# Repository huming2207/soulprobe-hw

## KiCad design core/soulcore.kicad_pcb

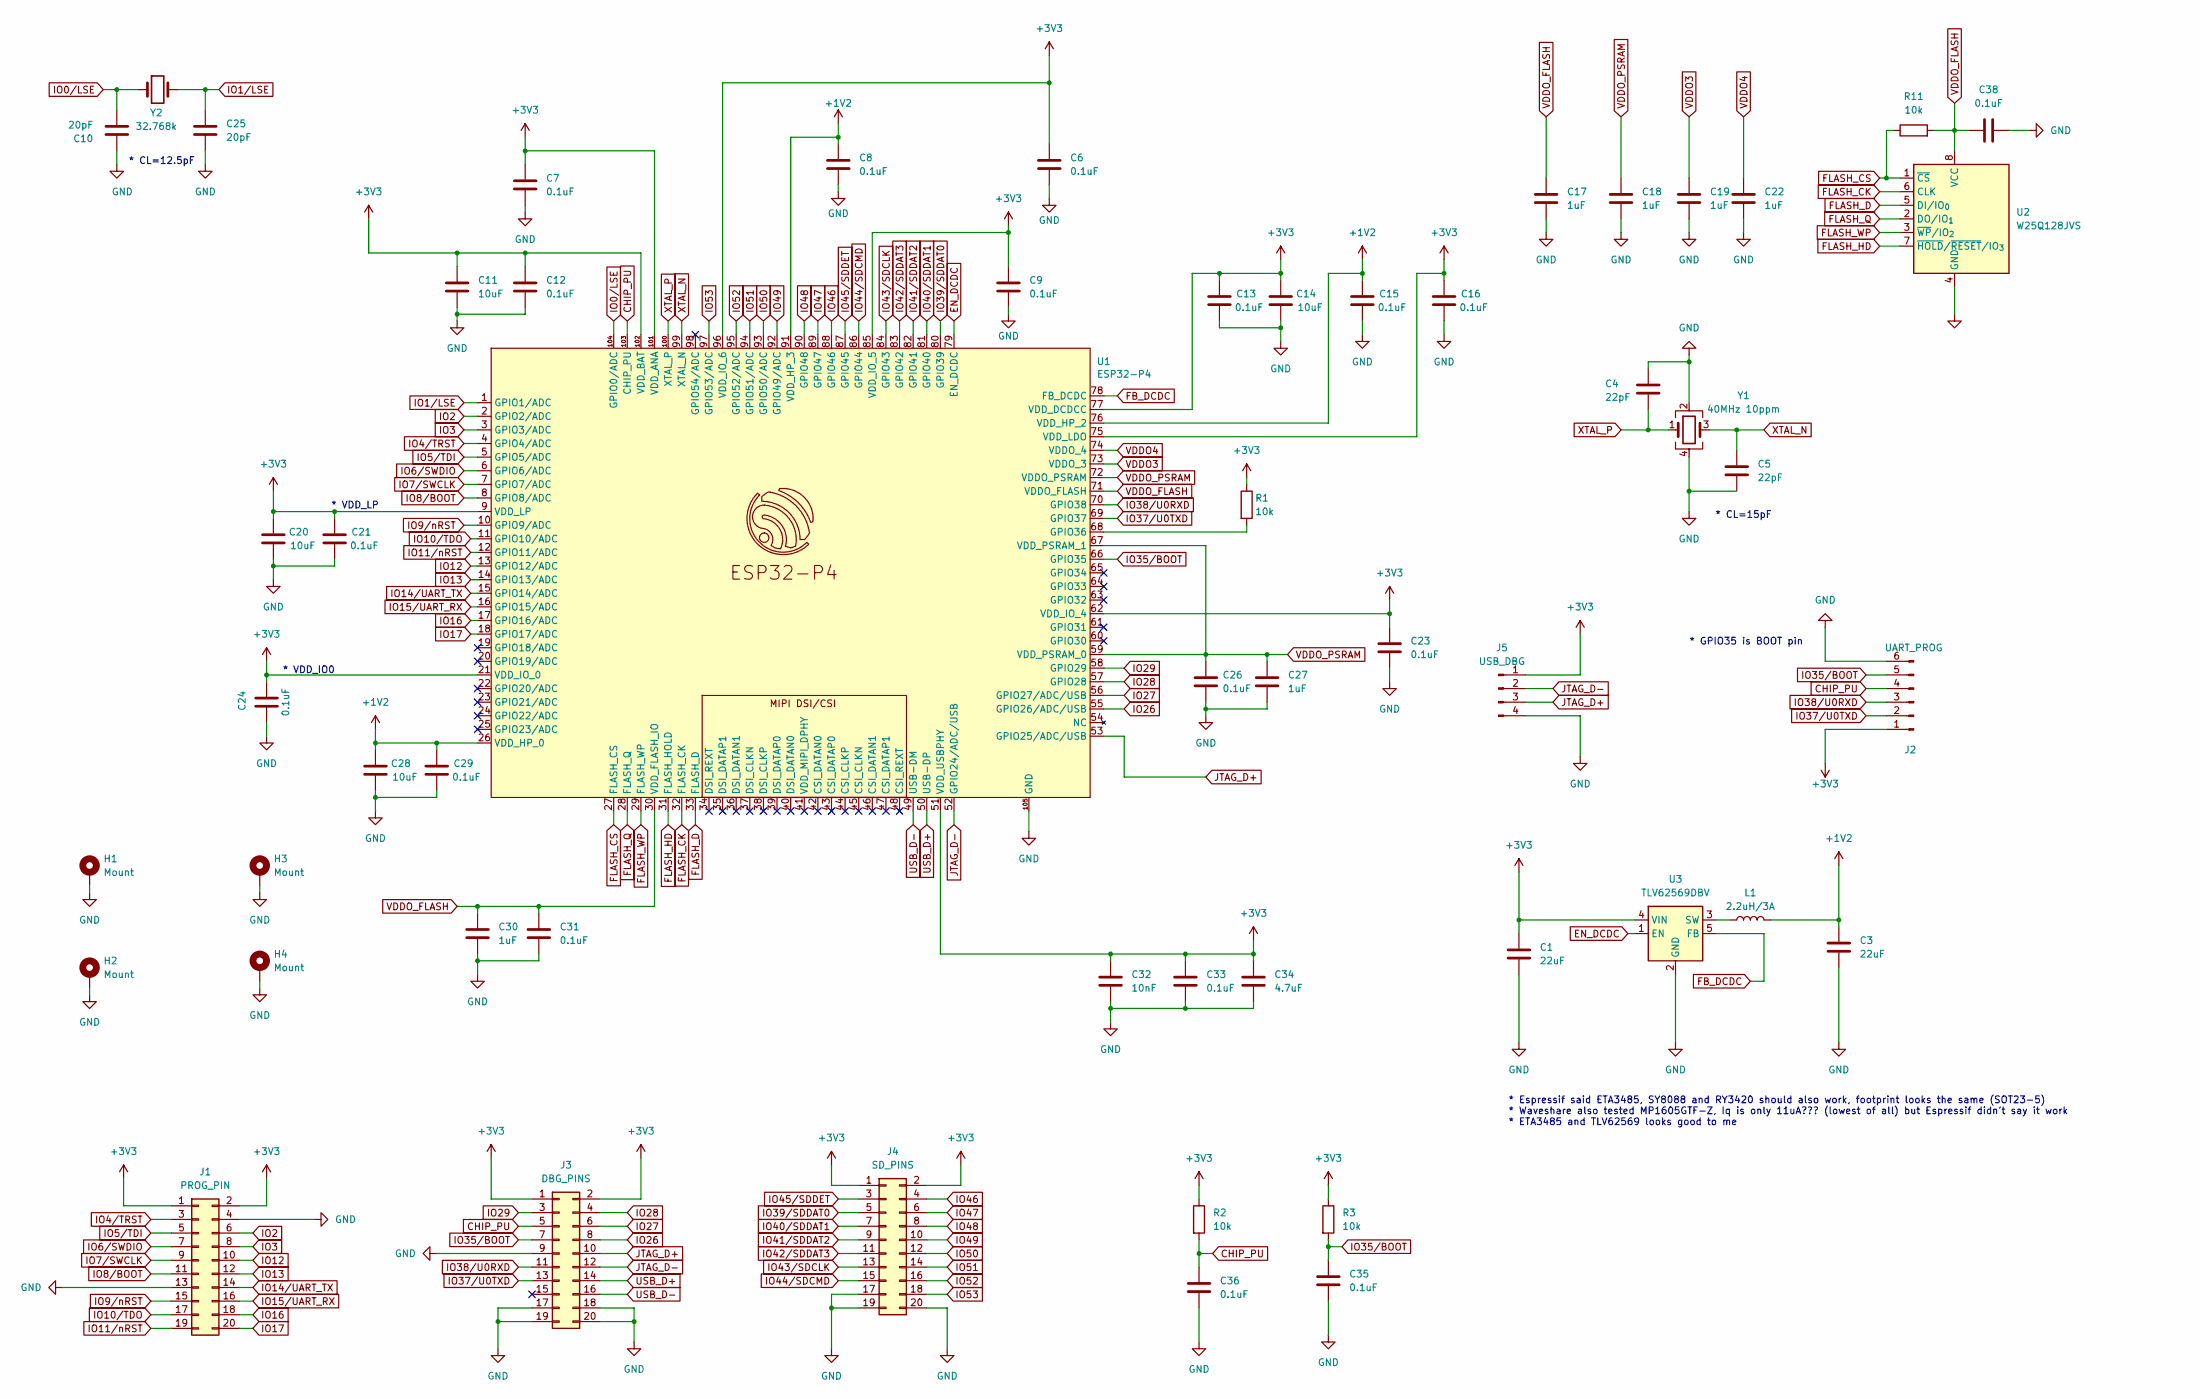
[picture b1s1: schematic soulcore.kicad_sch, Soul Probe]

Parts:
C1, C3: 22uF; C_0402_1005Metric; LCSC C59461
C4, C5: 22pF; C_0402_1005Metric; LCSC C1555
C6, C7, C8, C9, C12, C13, C15, C16, C21, C23, C24, C26, C29, C31, C33, C35, C36, C38: 0.1uF; C_0402_1005Metric; LCSC C1525
C10, C25: 20pF; C_0402_1005Metric; LCSC C1554
C11, C14, C20, C28: 10uF; C_0402_1005Metric; LCSC C19702
C17, C18, C19, C22, C27, C30: 1uF; C_0402_1005Metric; LCSC C15849
C32: 10nF; C_0402_1005Metric; LCSC C57112
C34: 4.7uF; C_0402_1005Metric; LCSC C19666
H1, H2, H3, H4: Mount; MountingHole_2.2mm_M2_Pad
J1: PROG_PIN; PinHeader_2x10_P1.27mm_Vertical_SMD
J2: UART_PROG; PinSocket_1x06_P2.00mm_Vertical
J3: DBG_PINS; PinHeader_2x10_P1.27mm_Vertical_SMD
J4: SD_PINS; PinHeader_2x10_P1.27mm_Vertical_SMD
J5: USB_DBG; PinSocket_1x04_P2.00mm_Vertical
L1: 2.2uH/3A; L_Changjiang_FTC322510S; LCSC C5832385
R1, R2, R3, R11: 10k; R_0402_1005Metric; LCSC C25744
U1: ESP32-P4; LCSC C22387510
U2: W25Q128JVS; SOIC-8_5.3x5.3mm_P1.27mm; LCSC C97521
U3: TLV62569DBV; SOT-23-5; LCSC C141836
Y1: 40MHz 10ppm; Crystal_SMD_2016-4Pin_2.0x1.6mm; LCSC C424432
Y2: 32.768k; Crystal_SMD_3215-2Pin_3.2x1.5mm; LCSC C32346

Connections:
+1V2: C3.1, C8.1, C15.1, C28.1, C29.1, L1.2, U1.26 (VDD_HP_0), U1.76 (VDD_HP_2), U1.91 (VDD_HP_3)
+3V3: C1.1, C6.1, C7.1, C9.1, C11.1, C12.1, C13.1, C14.1, C16.1, C20.1, C21.1, C23.1, C24.2, C32.1, C33.1, C34.1, J1.1, J1.2, J2.1, J3.1, J3.2, J4.1, J4.2, J5.1, R1.1, R2.1, R3.1, U1.9 (VDD_LP), U1.21 (VDD_IO_0), U1.51 (VDD_USBPHY), U1.62 (VDD_IO_4), U1.75 (VDD_LDO), U1.77 (VDD_DCDCC), U1.85 (VDD_IO_5), U1.96 (VDD_IO_6), U1.101 (VDD_ANA), U1.102 (VDD_BAT), U3.4 (VIN)
CHIP_PU: C36.1, J2.4, J3.5, R2.2, U1.103 (CHIP_PU)
EN_DCDC: U1.79 (EN_DCDC), U3.1 (EN)
FB_DCDC: U1.78 (FB_DCDC), U3.5 (FB)
FLASH_CK: U1.32 (FLASH_CK), U2.6 (CLK)
FLASH_CS: R11.1, U1.27 (FLASH_CS), U2.1 (~CS)
FLASH_D: U1.33 (FLASH_D), U2.5 (DI/IO_{0})
FLASH_HD: U1.31 (FLASH_HOLD), U2.7 (~HOLD/~RESET/IO_{3})
FLASH_Q: U1.28 (FLASH_Q), U2.2 (DO/IO_{1})
FLASH_WP: U1.29 (FLASH_WP), U2.3 (~WP/IO_{2})
GND: C1.2, C3.2, C4.1, C5.2, C6.2, C7.2, C8.2, C9.2, C10.1, C11.2, C12.2, C13.2, C14.2, C15.2, C16.2, C17.2, C18.2, C19.2, C20.2, C21.2, C22.2, C23.2, C24.1, C25.2, C26.2, C27.2, C28.2, C29.2, C30.2, C31.2, C32.2, C33.2, C34.2, C35.2, C36.2, C38.2, H1.1, H2.1, H3.1, H4.1, J1.4, J1.13, J2.6, J3.9, J3.17, J3.18, J3.19, J3.20, J4.17, J4.19, J4.20, J5.4, U1.105 (GND), U2.4 (GND), U3.2 (GND), Y1.2, Y1.4
IO0/LSE: C10.2, U1.104 (GPIO0/ADC), Y2.1
IO1/LSE: C25.1, U1.1 (GPIO1/ADC), Y2.2
IO2: J1.6, U1.2 (GPIO2/ADC)
IO3: J1.8, U1.3 (GPIO3/ADC)
IO4/TRST: J1.3, U1.4 (GPIO4/ADC)
IO5/TDI: J1.5, U1.5 (GPIO5/ADC)
IO6/SWDIO: J1.7, U1.6 (GPIO6/ADC)
IO7/SWCLK: J1.9, U1.7 (GPIO7/ADC)
IO8/BOOT: J1.11, U1.8 (GPIO8/ADC)
IO9/nRST: J1.15, U1.10 (GPIO9/ADC)
IO10/TDO: J1.17, U1.11 (GPIO10/ADC)
IO11/nRST: J1.19, U1.12 (GPIO11/ADC)
IO12: J1.10, U1.13 (GPIO12/ADC)
IO13: J1.12, U1.14 (GPIO13/ADC)
IO14/UART_TX: J1.14, U1.15 (GPIO14/ADC)
IO15/UART_RX: J1.16, U1.16 (GPIO15/ADC)
IO16: J1.18, U1.17 (GPIO16/ADC)
IO17: J1.20, U1.18 (GPIO17/ADC)
IO26: J3.8, U1.55 (GPIO26/ADC/USB)
IO27: J3.6, U1.56 (GPIO27/ADC/USB)
IO28: J3.4, U1.57 (GPIO28)
IO29: J3.3, U1.58 (GPIO29)
IO35/BOOT: C35.1, J2.5, J3.7, R3.2, U1.66 (GPIO35)
IO37/U0TXD: J2.2, J3.13, U1.69 (GPIO37)
IO38/U0RXD: J2.3, J3.11, U1.70 (GPIO38)
IO39/SDDAT0: J4.5, U1.80 (GPIO39)
IO40/SDDAT1: J4.7, U1.81 (GPIO40)
IO41/SDDAT2: J4.9, U1.82 (GPIO41)
IO42/SDDAT3: J4.11, U1.83 (GPIO42)
IO43/SDCLK: J4.13, U1.84 (GPIO43)
IO44/SDCMD: J4.15, U1.86 (GPIO44)
IO45/SDDET: J4.3, U1.87 (GPIO45)
IO46: J4.4, U1.88 (GPIO46)
IO47: J4.6, U1.89 (GPIO47)
IO48: J4.8, U1.90 (GPIO48)
IO49: J4.10, U1.92 (GPIO49/ADC)
IO50: J4.12, U1.93 (GPIO50/ADC)
IO51: J4.14, U1.94 (GPIO51/ADC)
IO52: J4.16, U1.95 (GPIO52/ADC)
IO53: J4.18, U1.97 (GPIO53/ADC)
JTAG_D+: J3.10, J5.3, U1.53 (GPIO25/ADC/USB)
JTAG_D-: J3.12, J5.2, U1.52 (GPIO24/ADC/USB)
unnamed: R1.2, U1.68 (GPIO36)
unnamed: L1.1, U3.3 (SW)
USB_D+: J3.14, U1.50 (USB-DP)
USB_D-: J3.16, U1.49 (USB-DM)
VDDO3: C19.1, U1.73 (VDDO_3)
VDDO4: C22.1, U1.74 (VDDO_4)
VDDO_FLASH: C17.1, C30.1, C31.1, C38.1, R11.2, U1.30 (VDD_FLASH_IO), U1.71 (VDDO_FLASH), U2.8 (VCC)
VDDO_PSRAM: C18.1, C26.1, C27.1, U1.59 (VDD_PSRAM_0), U1.67 (VDD_PSRAM_1), U1.72 (VDDO_PSRAM)
XTAL_N: C5.1, U1.99 (XTAL_N), Y1.3
XTAL_P: C4.2, U1.100 (XTAL_P), Y1.1

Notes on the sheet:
* GPIO35 is BOOT pin
* Espressif said ETA3485, SY8088 and RY3420 should also work, footprint looks the same (SOT23-5) * Waveshare also tested MP1605GTF-Z, Iq is only 11uA??? (lowest of all) but Espressif didn't say it work * ETA3485 and TLV62569 looks good to me
* CL=12.5pF
* CL=15pF
* VDD_LP
* VDD_IO0

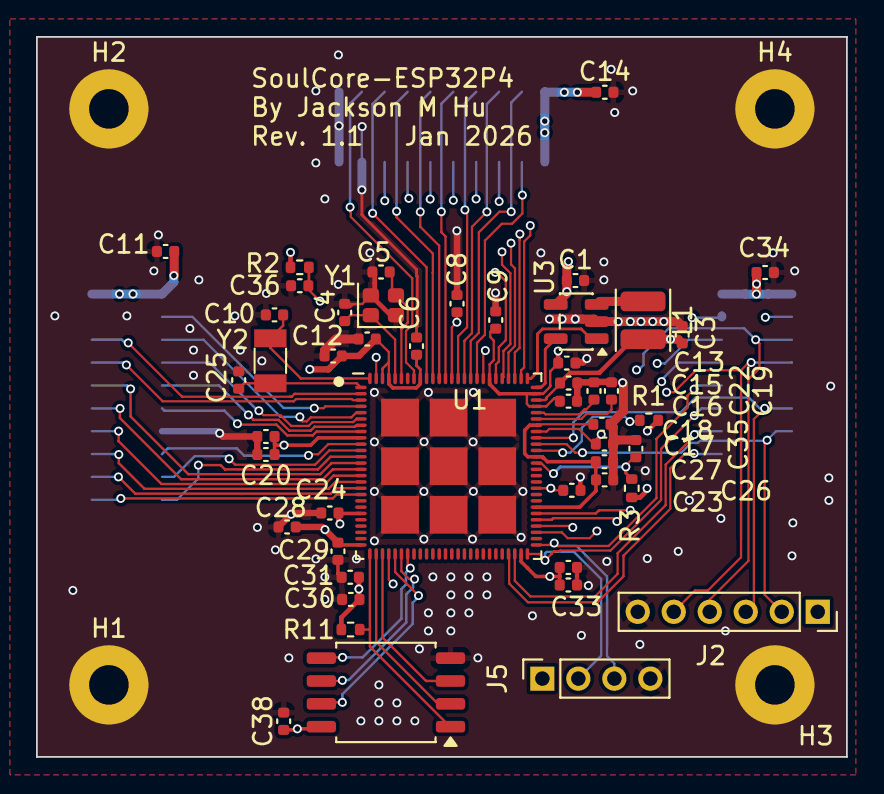
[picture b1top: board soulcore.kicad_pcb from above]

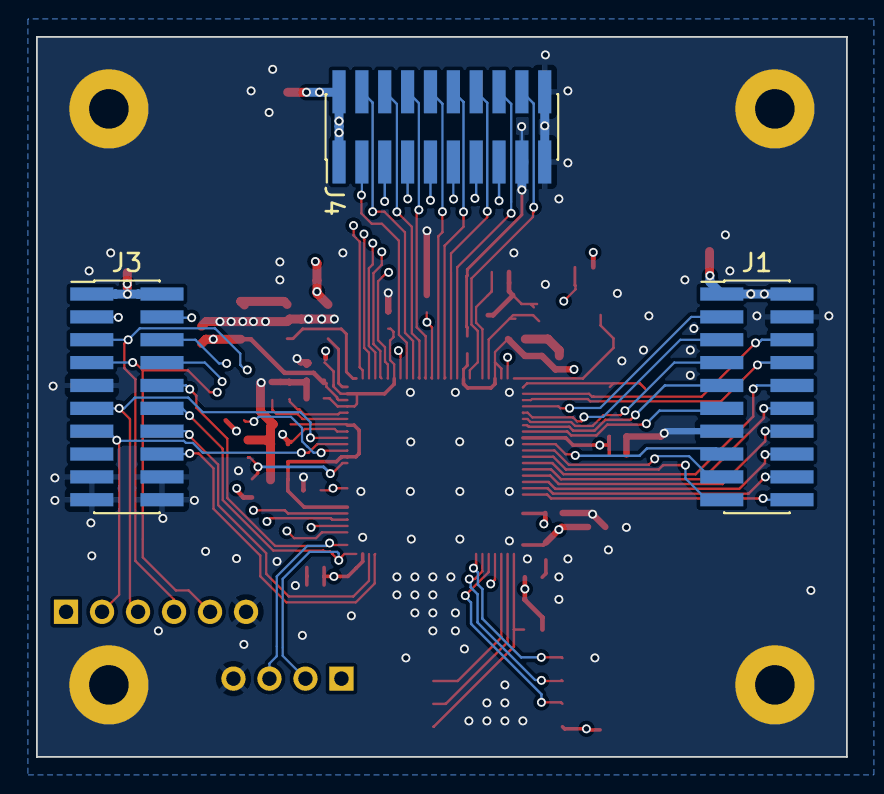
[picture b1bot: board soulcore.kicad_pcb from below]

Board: 4 copper layers, 45.0 x 40.0 mm, 55 parts (3 on the bottom side), 64 nets.

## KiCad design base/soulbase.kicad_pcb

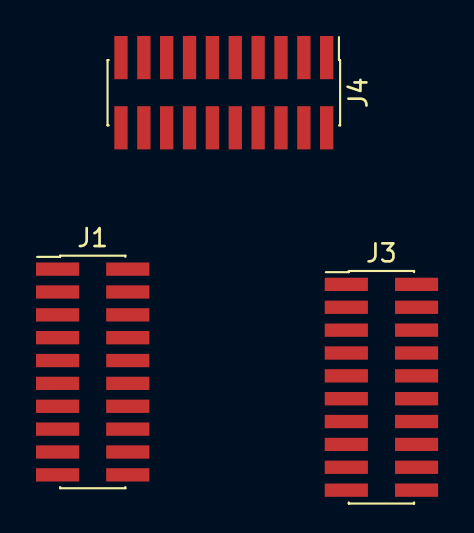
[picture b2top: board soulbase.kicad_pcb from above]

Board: 2 copper layers, 3 parts (0 on the bottom side), 2 nets, no tracks yet.

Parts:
J1: PROG_PIN; PinHeader_2x10_P1.27mm_Vertical_SMD
J3: DBG_PINS; PinHeader_2x10_P1.27mm_Vertical_SMD
J4: SD_PINS; PinHeader_2x10_P1.27mm_Vertical_SMD

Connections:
+3V3: J1.1, J1.2, J3.1, J3.2, J3.3, J3.4, J4.1, J4.2
GND: J1.3, J1.11, J1.14, J1.15, J3.10, J3.17, J3.18, J3.19, J3.20, J4.18, J4.19, J4.20

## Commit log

2025-11-27 Init
2025-11-27 Add external libs
2025-11-27 Split schematic
2025-11-28 Finish off schematic
2025-11-28 Typo fix
2025-11-28 Assign footprint
2025-11-29 Refine footprint matching
2025-12-05 Rev 1
2025-12-07 Rev 1 - rework traces
2025-12-08 Rev 1 - rename to soulcore
2026-01-01 Rev 1.1

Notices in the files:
core/soulcore.kicad_sch:
By Jackson Ming Hu  Copright (C) 2025
